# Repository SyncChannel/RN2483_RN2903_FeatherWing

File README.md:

# RN2483_RN2903_FeatherWing

This FeatherWing adds a Microchip RN2483 or RN2903 LoRaWAN module to Adafruit Feather. It also includes a power LED and an LED connected to GPIO10 of the RN module for debugging or status indication. The parts values are shown in the schematic.

This PCB design is tested and functional. BUT! I DO NOT recommend that you use it. The width of the module and the spacing of the Feather headers prevents a proper footprint for the RN module from being used. The pads are very small and very close to the headers. Even with a small iron tip, it is extremely difficult to hand solder. You MUST check carefully for bridges between the castellations of the module and header pins with magnification after soldering it.

Upon request, I have uploaded the Eagle files to this repo. I will not be doing a blog post article on this one.

Dan Watson

syncchannel.blogspot.com

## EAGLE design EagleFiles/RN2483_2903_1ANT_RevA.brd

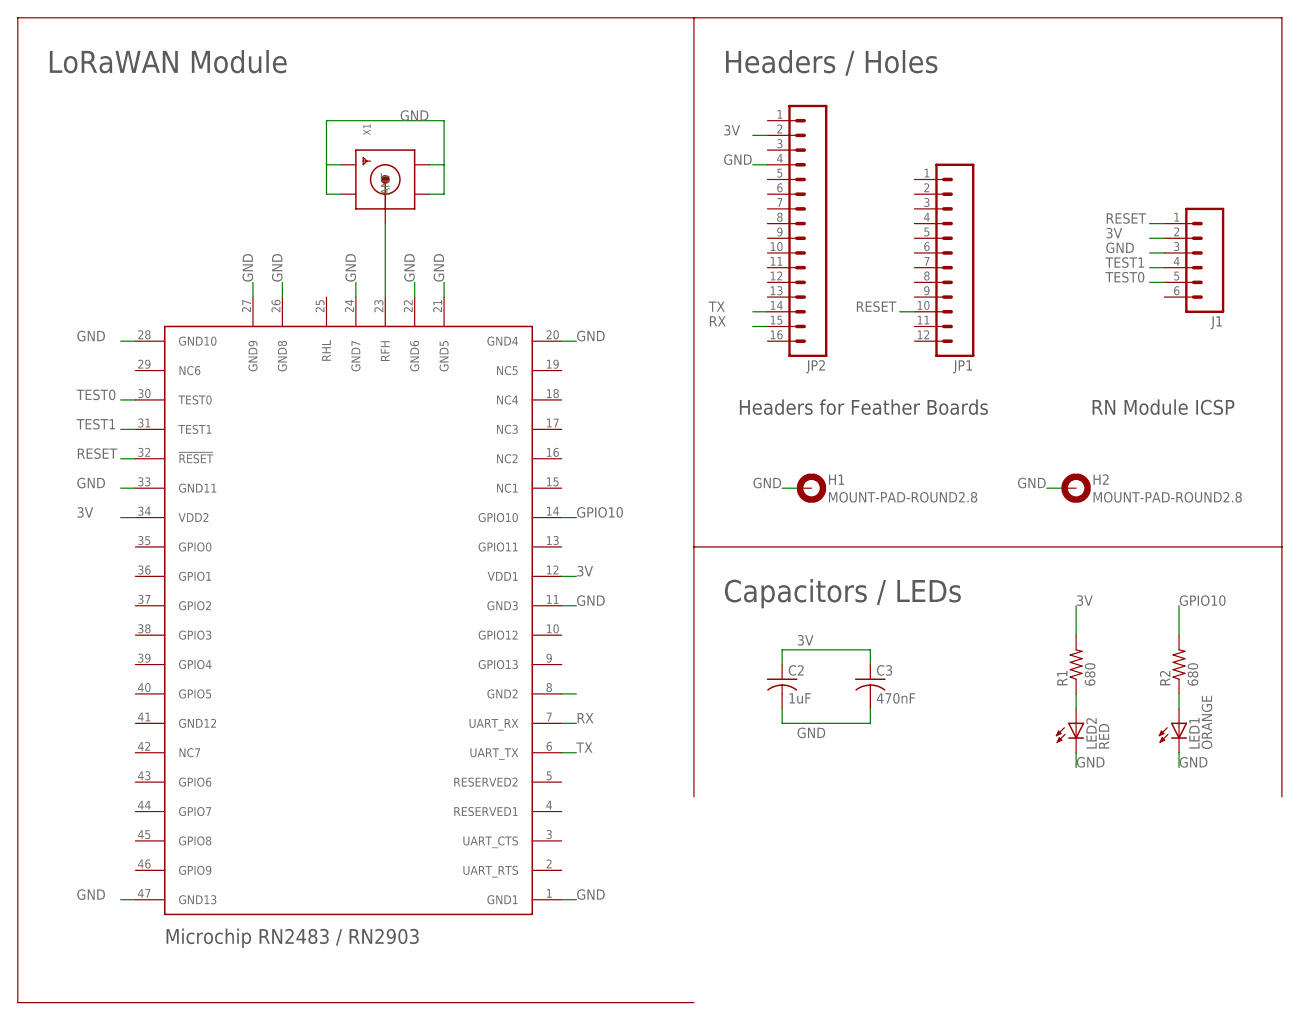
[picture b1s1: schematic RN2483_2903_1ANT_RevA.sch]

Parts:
C2: 1uF; C0603
C3: 470nF; C0603
H1, H2: MOUNT-PAD-ROUND2.8; 2,8-PAD
J1: M06SILK_FEMALE_PTH; 1X06
JP1: M12NO_SILK; 1X12_NO_SILK
JP2: M161X16_NO_SILK; 1X16_NO_SILK
LED1: ORANGE; CHIPLED_0805
LED2: RED; CHIPLED_0805
R1, R2: 680; R0603
U$2: RN2483/2903
X1: SMACONNECTOR_EDGE; SMA_EDGELAUNCH

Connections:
3V: C2.1, C3.1, J1.2, JP2.2, R1.2, U$2.12 (VDD1), U$2.34 (VDD2)
GND: C2.2, C3.2, H1.B2,8, H2.B2,8, J1.3, JP2.4, LED1.C, LED2.C, U$2.1 (GND1), U$2.11 (GND3), U$2.20 (GND4), U$2.21 (GND5), U$2.22 (GND6), U$2.24 (GND7), U$2.26 (GND8), U$2.27 (GND9), U$2.28 (GND10), U$2.33 (GND11), U$2.47 (GND13), X1.GND@1 (GND4), X1.GND@2 (GND3), X1.GND@3 (GND2), X1.GND@4 (GND1)
GPIO10: R2.2, U$2.14 (GPIO10)
unnamed: LED1.A, R2.1
unnamed: U$2.23 (RFH), X1.P (ANT)
unnamed: LED2.A, R1.1
RESET: J1.1, JP1.10, U$2.32 (!RESET)
RX: JP2.15, U$2.7 (UART_RX)
TEST0: J1.5, U$2.30 (TEST0)
TEST1: J1.4, U$2.31 (TEST1)
TX: JP2.14, U$2.6 (UART_TX)

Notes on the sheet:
Headers for Feather Boards
Headers / Holes
Capacitors / LEDs
RN Module ICSP
LoRaWAN Module
Microchip RN2483 / RN2903

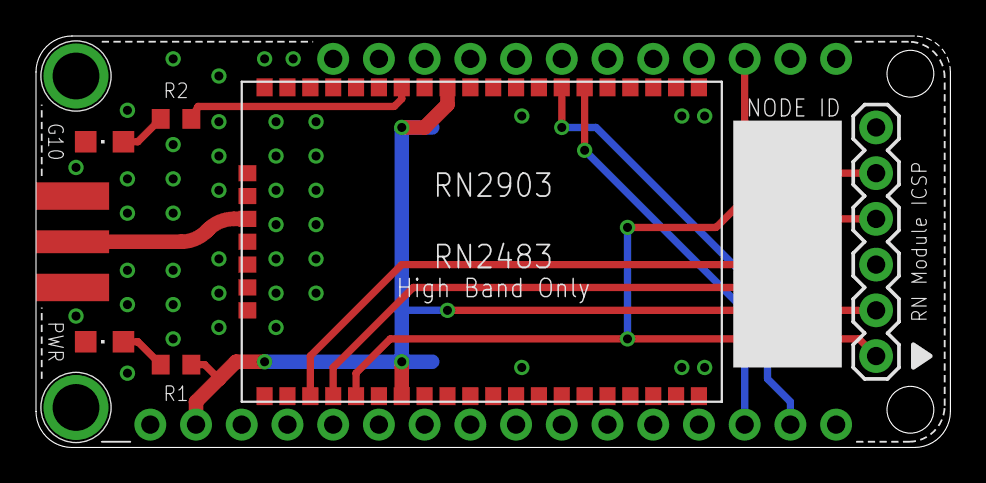
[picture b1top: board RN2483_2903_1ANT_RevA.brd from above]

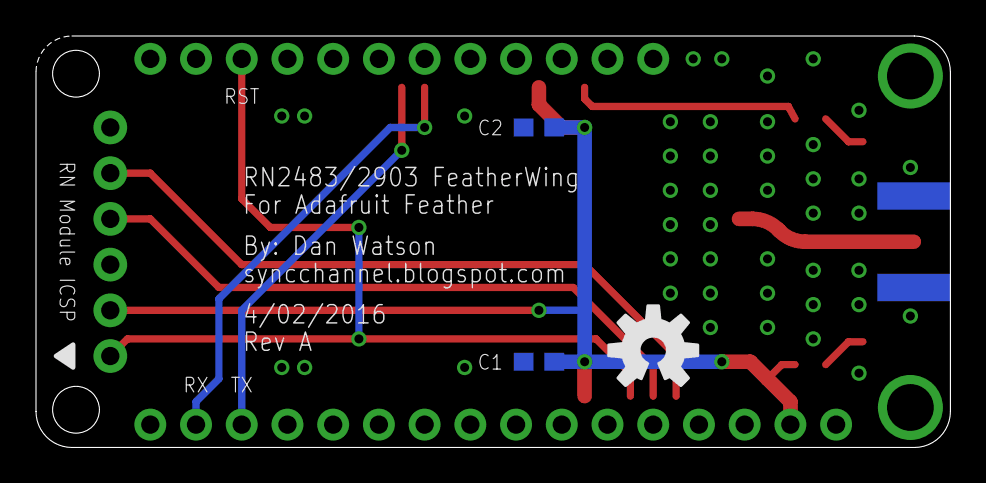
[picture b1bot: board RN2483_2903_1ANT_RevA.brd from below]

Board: 2 copper layers, 50.8 x 22.9 mm, 14 parts (3 on the bottom side), 11 nets.

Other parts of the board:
U$1: OSHW-LOGO-M

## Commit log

2016-05-17 :confetti_ball: Added .gitattributes & .gitignore files
2016-05-17 Added Eagle Files
2016-05-18 Added Readme

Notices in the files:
parts and their libraries:
SparkFun-Connectors: Licensing: Creative Commons ShareAlike 4.0 International - https://creativecommons.org/licenses/by-sa/4.0
